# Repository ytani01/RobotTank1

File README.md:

# Robot Tank

Robot Tank Package

## setup

### スワップファイル拡張

``` shell
sudo vi /etc/dphys-swapfile
-----
CONF_SWAPSIZE=1024
-----
sudo service dphys-swapfile restart
```

### 

### mjpg-streamer

[mjpg-streamer](./docs/mjpg-streamer.md)

## Reference

* [Python: 自作ライブラリのパッケージングについて](https://blog.amedama.jp/entry/packaging-python)
* [setuptools —Pythonパッケージ作成](https://heavywatal.github.io/python/setuptools.html)

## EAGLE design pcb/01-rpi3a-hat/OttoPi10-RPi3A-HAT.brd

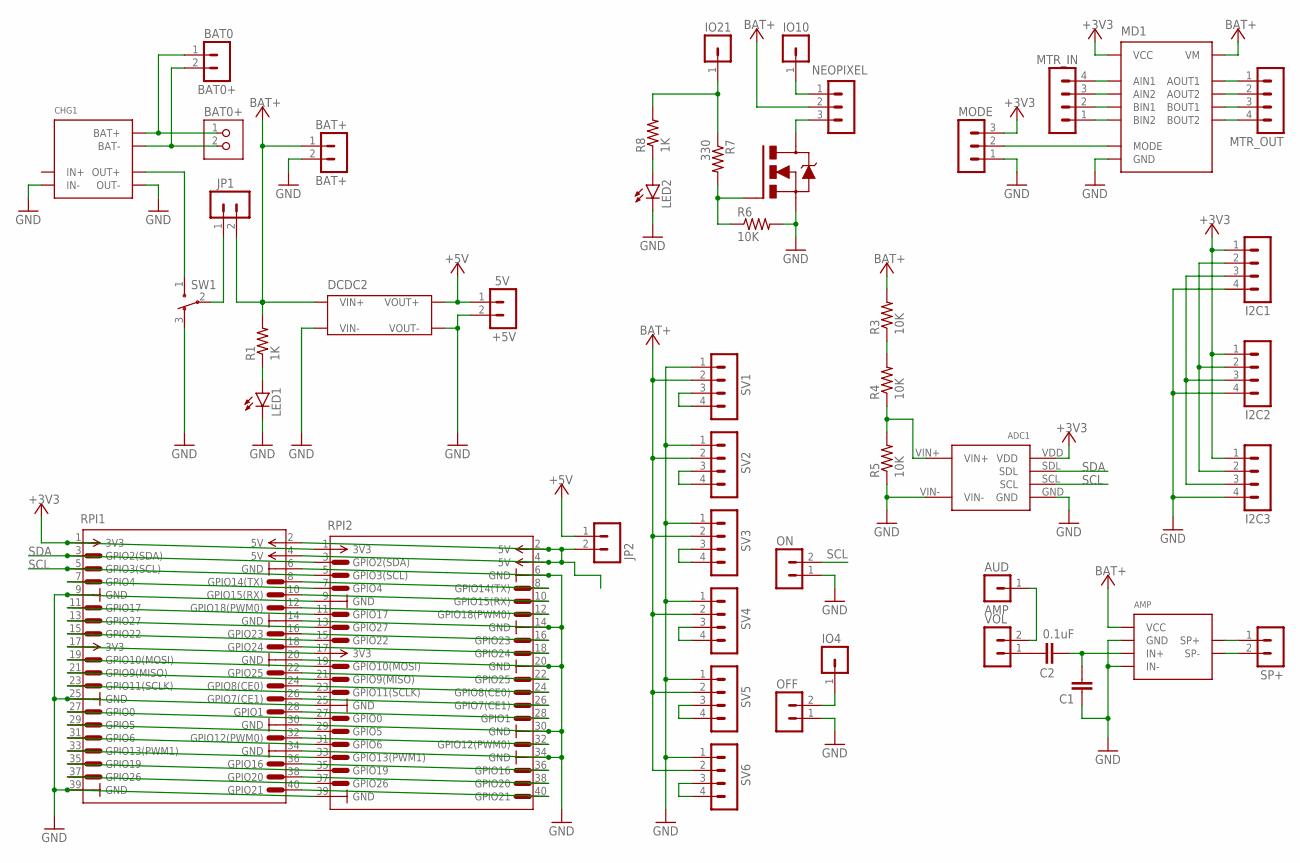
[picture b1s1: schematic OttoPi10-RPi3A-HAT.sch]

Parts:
+5V: 5V; PINHEAD-MA02-1
ADC1: MCP3425MOD
AMP: AMP; PAM8012MOD-A
AUD: AMP; PINHEAD-MA01-1
BAT0: BAT0+; PINHEAD-MA02-1
BAT0+: JST-PH2
BAT+: BAT+; PINHEAD-MA02-1
C1: C-EU025-024X044; C025-024X044
C2: 0.1uF; C025-024X044
CHG1: TP4056MOD1
DCDC2: DCDC-SX1308-MOD1
I2C1, I2C2, I2C3: PINHEAD-MA04-1
IO4, IO10, IO21: PINHEAD-MA01-1
JP1, JP2: PINHEAD-MA02-1
LED1, LED2: LED3MM
MD1: DRV8835MOD
MODE: PINHEAD-MA03-1
MTR_IN: PINHEAD-MA04-1
MTR_OUT: PINHEAD-MA04-1
NEOPIXEL: PINHEAD-MA03-1
OFF: PINHEAD-MA02-1
ON: PINHEAD-MA02-1
Q1: 2SK4017; MOSFET-1
R1, R8: 1K; 0204/7
R3, R4, R5, R6: 10K; 0204/7
R7: 330; 0204/7
RPI1, RPI2: RPI-PIN
SP+: PINHEAD-MA02-1
SV1, SV2, SV3, SV4, SV5, SV6: PINHEAD-MA04-1
SW1: SW3-1
VOL: PINHEAD-MA02-1

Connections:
+3V3: ADC1.VDD, I2C1.1, I2C2.1, I2C3.1, MD1.VCC, MODE.3, RPI1.1 (3V3), RPI2.1 (3V3)
+5V: +5V.1, DCDC2.VOUT+, JP2.1
+5V_RPI: JP2.2, RPI1.2 (5V), RPI1.4 (5V), RPI2.2 (5V), RPI2.4 (5V)
AIN1: MD1.AIN1, MTR_IN.4
AIN2: MD1.AIN2, MTR_IN.3
AOUT1: MD1.AOUT1, MTR_OUT.1
AOUT2: MD1.AOUT2, MTR_OUT.2
AUDIO0: AUD.1, VOL.2
AUDIO1: AMP.IN+, C1.2, C2.1
BAT+: AMP.V+ (VCC), BAT+.1, DCDC2.VIN+, JP1.2, MD1.VM, NEOPIXEL.2, R1.2, R3.2, SV1.2, SV2.2, SV3.2, SV4.2, SV5.2, SV6.2
BAT+0: BAT0.1, BAT0+.1, CHG1.BAT+
BAT+1: CHG1.OUT+, SW1.1
BAT+2: JP1.1, SW1.2
BAT-0: BAT0.2, BAT0+.2, CHG1.BAT-
BIN1: MD1.BIN1, MTR_IN.2
BIN2: MD1.BIN2, MTR_IN.1
BOUT1: MD1.BOUT1, MTR_OUT.3
BOUT2: MD1.BOUT2, MTR_OUT.4
GND: +5V.2, ADC1.GND, ADC1.VIN-, AMP.GND, AMP.IN-, BAT+.2, C1.1, CHG1.IN-, CHG1.OUT-, DCDC2.VIN-, DCDC2.VOUT-, I2C1.4, I2C2.4, I2C3.4, LED1.K (C), LED2.K (C), MD1.GND, MODE.1, OFF.1, ON.1, Q1.S, R5.1, R6.2, RPI1.6 (GND), RPI1.9 (GND), RPI1.14 (GND), RPI1.20 (GND), RPI1.25 (GND), RPI1.30 (GND), RPI1.34 (GND), RPI1.39 (GND), RPI2.6 (GND), RPI2.9 (GND), RPI2.14 (GND), RPI2.20 (GND), RPI2.25 (GND), RPI2.30 (GND), RPI2.34 (GND), RPI2.39 (GND), SV1.1, SV2.1, SV3.1, SV4.1, SV5.1, SV6.1, SW1.3
GPIO10: RPI1.17 (3V3), RPI2.17 (3V3)
MODE: MD1.MODE, MODE.2
unnamed: Q1.G, R6.1, R7.2
unnamed: NEOPIXEL.3, Q1.D
unnamed: LED1.A, R1.1
unnamed: IO21.1, R7.1, R8.2
unnamed: RPI1.7 (GPIO4), RPI2.7 (GPIO4)
unnamed: IO10.1, NEOPIXEL.1
unnamed: RPI1.11 (GPIO17), RPI2.11 (GPIO17)
unnamed: RPI1.13 (GPIO27), RPI2.13 (GPIO27)
unnamed: RPI1.15 (GPIO22), RPI2.15 (GPIO22)
unnamed: RPI1.23 (GPIO11(SCLK)), RPI2.23 (GPIO11(SCLK))
unnamed: RPI1.19 (GPIO10(MOSI)), RPI2.19 (GPIO10(MOSI))
unnamed: RPI1.21 (GPIO9(MISO)), RPI2.21 (GPIO9(MISO))
unnamed: C2.2, VOL.1
unnamed: LED2.A, R8.1
unnamed: RPI1.8 (GPIO14(TX)), RPI2.8 (GPIO14(TX))
unnamed: RPI1.10 (GPIO15(RX)), RPI2.10 (GPIO15(RX))
unnamed: RPI1.12 (GPIO18(PWM0)), RPI2.12 (GPIO18(PWM0))
unnamed: RPI1.16 (GPIO23), RPI2.16 (GPIO23)
unnamed: RPI1.18 (GPIO24), RPI2.18 (GPIO24)
unnamed: RPI1.22 (GPIO25), RPI2.22 (GPIO25)
unnamed: IO4.1, OFF.2
unnamed: R3.1, R4.2
unnamed: ADC1.VIN+, R4.1, R5.2
unnamed: RPI1.24 (GPIO8(CE0)), RPI2.24 (GPIO8(CE0))
unnamed: RPI1.26 (GPIO7(CE1)), RPI2.26 (GPIO7(CE1))
unnamed: RPI1.27 (GPIO0), RPI2.27 (GPIO0)
unnamed: RPI1.28 (GPIO1), RPI2.28 (GPIO1)
unnamed: RPI1.29 (GPIO5), RPI2.29 (GPIO5)
unnamed: RPI1.31 (GPIO6), RPI2.31 (GPIO6)
unnamed: RPI1.32 (GPIO12(PWM0)), RPI2.32 (GPIO12(PWM0))
unnamed: RPI1.33 (GPIO13(PWM1)), RPI2.33 (GPIO13(PWM1))
unnamed: RPI1.35 (GPIO19), RPI2.35 (GPIO19)
unnamed: RPI1.36 (GPIO16), RPI2.36 (GPIO16)
unnamed: RPI1.37 (GPIO26), RPI2.37 (GPIO26)
unnamed: RPI1.38 (GPIO20), RPI2.38 (GPIO20)
unnamed: RPI1.40 (GPIO21), RPI2.40 (GPIO21)
unnamed: SV2.3, SV2.4
unnamed: SV3.3, SV3.4
unnamed: SV4.3, SV4.4
unnamed: SV1.3, SV1.4
unnamed: SV5.3, SV5.4
unnamed: SV6.3, SV6.4
SCL: ADC1.SCL, I2C1.3, I2C2.3, I2C3.3, ON.2, RPI1.5 (GPIO3(SCL)), RPI2.5 (GPIO3(SCL))
SDA: ADC1.SDL, I2C1.2, I2C2.2, I2C3.2, RPI1.3 (GPIO2(SDA)), RPI2.3 (GPIO2(SDA))
SP+: AMP.SP+@1 (SP+), SP+.1
SP-: AMP.SP-@1 (SP-), SP+.2

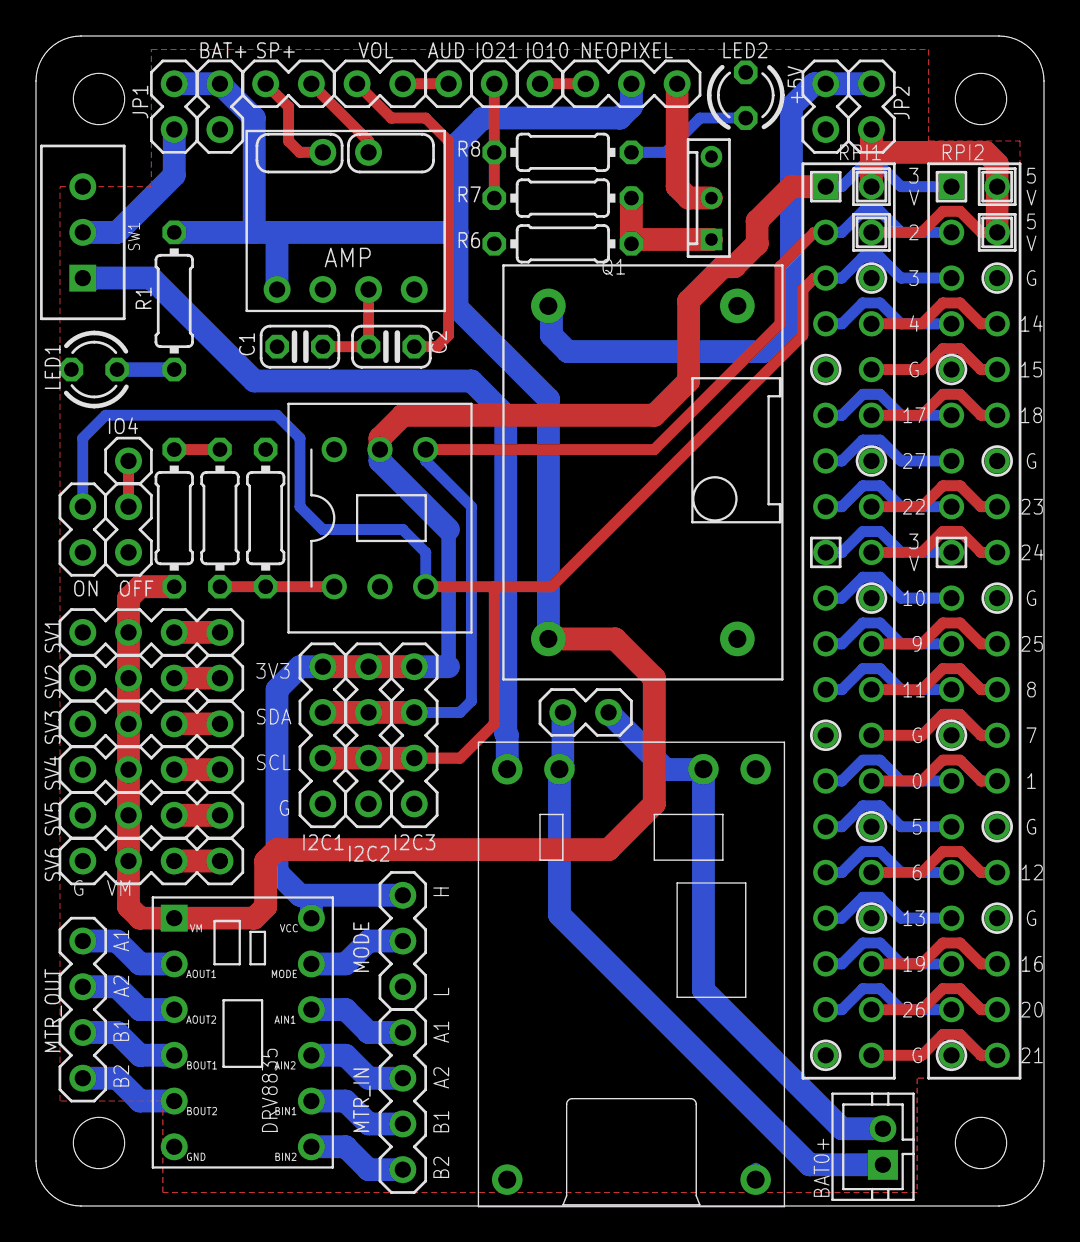
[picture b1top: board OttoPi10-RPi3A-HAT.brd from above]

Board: 2 copper layers, 56.0 x 65.0 mm, 47 parts (0 on the bottom side), 67 nets.

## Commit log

2023-01-24 .gitignore
2023-01-24 Add: test_dc_mtr.py
2023-01-24 UPD: test_dc_mtr.py
2023-01-24 ADD: test_dc_mtr_n.py
2023-01-25 UPD: dc_mtr.py and test_dc_mtr_n.py
2023-01-29 UPD: DcMtr/
2023-01-29 UPD: dc_mtr_server.py
2023-01-29 UPD: DcMtr/README.md
2023-01-30 ADD: dc_mtr_clinet
2023-01-30 UPD: dc_mtr_clinet
2023-01-31 UPD: test_dc_mtr_client.py
2023-02-01 ADD: AbShutter/
2023-02-01 UPD: test_ab_shutter.py
2023-02-01 ADD: start scripts
2023-02-02 UPD: AbShutter/
2023-02-02 UPD: rename "dc_mtr" to "dcmtr"
2023-02-05 UPD:
2023-02-09 ADD: BtSerial/
2023-02-09 UPD: BtSerial/
2023-02-11 UPD: BtSerial/btserial/
2023-02-11 ADD: body/
2023-02-11 UPD: BtKbd and DcMtr
2023-02-11 ADD: body02/
2023-02-14 ADD: Bt8BitDoZero2/
2023-02-14 ADD: start_bt8bitdozero2.sh
2023-02-14 FIX: start_bt8bitdozero2.sh
2023-02-14 UPD: Bt8BitDoZero2
2023-02-15 ADD: DistanceVL530X
2023-02-16 UPD: bt8bitdozero2/test_robottank.py etc
2023-02-16 UPD: DistanceVL53L0X
2023-02-16 UPD: DistanceVL53L0X/distancevl53l0x
2023-02-16 ADD: distancevl53l0x/test_robottankauto.py
2023-02-17 ADD: start_auto.sh
2023-02-17 UPD: DistanceVL53L0X/
2023-02-17 ADD: Bt8BitDoZero2N class
2023-02-17 UPD: start scripts
2023-02-17 UPD: test_robottankauto.py
2023-02-17 ADD: VL53L0X Client/Server
2023-02-17 UPD: auto
2023-02-18 ADD: Bt8BitDoZero2.pushed()
2023-02-19 ADD: TcpClientServer/
2023-02-19 ADD: CmdClientServer/
2023-02-19 ADD: robot_tank_auto.py
2023-02-20 UPD: robot_tank_auto.py
2023-02-20 UPD: Auto Pilot
2023-02-21 UPD: Auto Pilot and more
2023-02-21 UPD: CmdClientServer
2023-02-21 ADD: mjpg-streamer
2023-02-22 UPD: robottank_auto.py
2023-02-22 ADD: getkey.py
2023-02-23 UPD: boot scripts
2023-02-23 ADD: Bt8BitDoZero2/sample1.py
2023-02-24 UPD: DistanceVL53L0X/README.md
2023-02-25 UPD: buttons
2023-02-25 UPD: DcMtr Client/Server
2023-02-25 UPD: reboot
2023-03-02 UPD: boot etc.
2023-03-02 UPD: crontab.sample: slack-ipaddr.sh
2023-03-04 UPD: pcb/
2023-03-05 UPD: Bt8BitDoZero2/README.md
2023-03-05 UPD: start_*.sh
2023-03-05 UPD: mjpg-streamer
2023-03-06 UPD: pcb
